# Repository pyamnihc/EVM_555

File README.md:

# EVM_555
The schematic and pcb are "a faithful and functional transistor-scale replica of the NE555 timer integrated circuit" from [a kit by Evil Mad Scientist](https://shop.evilmadscientist.com/productsmenu/922)

The schematic simulates the 555 timer as a astable multivibrator

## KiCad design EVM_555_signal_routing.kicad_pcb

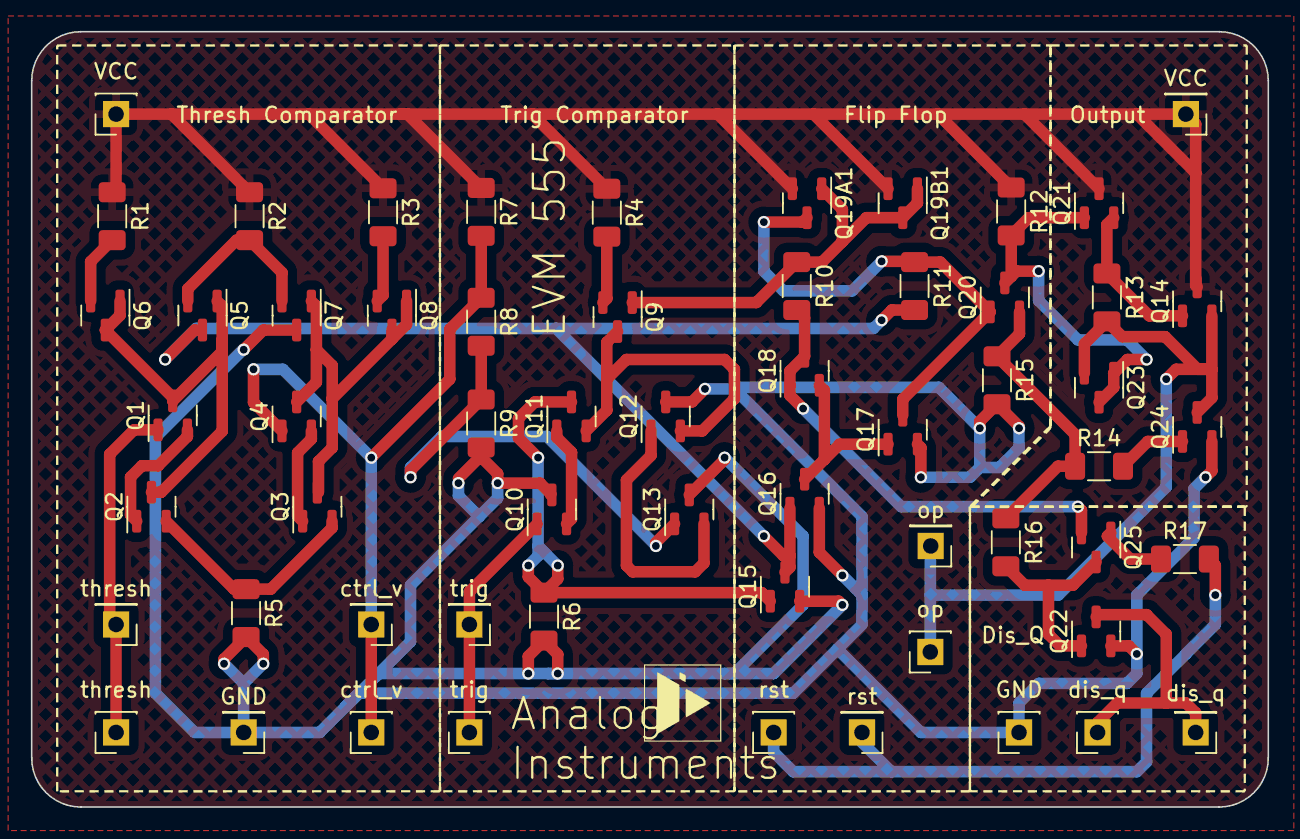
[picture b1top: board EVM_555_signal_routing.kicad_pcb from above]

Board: 2 copper layers, 80.0 x 50.2 mm, 59 parts (0 on the bottom side), 33 nets.

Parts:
J1: GND; PinHeader_1x01_P2.54mm_Vertical
J1A1: GND; PinSocket_1x01_P2.54mm_Vertical
J2: trig; PinHeader_1x01_P2.54mm_Vertical
J2A1: trig; PinSocket_1x01_P2.54mm_Vertical
J3: op; PinHeader_1x01_P2.54mm_Vertical
J3A1: op; PinSocket_1x01_P2.54mm_Vertical
J4: rst; PinHeader_1x01_P2.54mm_Vertical
J4A1: rst; PinSocket_1x01_P2.54mm_Vertical
J5: ctrl_v; PinHeader_1x01_P2.54mm_Vertical
J5A1: ctrl_v; PinSocket_1x01_P2.54mm_Vertical
J6: thresh; PinHeader_1x01_P2.54mm_Vertical
J6A1: thresh; PinSocket_1x01_P2.54mm_Vertical
J7: dis_q; PinHeader_1x01_P2.54mm_Vertical
J7A1: dis_q; PinSocket_1x01_P2.54mm_Vertical
J8: VCC; PinHeader_1x01_P2.54mm_Vertical
J8A1: VCC; PinSocket_1x01_P2.54mm_Vertical
Q1, Q2, Q3, Q4, Q14, Q15, Q16, Q17, Q18, Q20, Q21, Q22, Q24: MMBT3904; SOT-23
Q5, Q6, Q7, Q8, Q9, Q10, Q11, Q12, Q13, Q19A1, Q19B1, Q23, Q25: MMBT3906; SOT-23
R1, R3, R7, R8, R9, R11, R15: 4.7k; R_1206_3216Metric_Pad1.30x1.75mm_HandSolder
R2: 820; R_1206_3216Metric_Pad1.30x1.75mm_HandSolder
R4: 1k; R_1206_3216Metric_Pad1.30x1.75mm_HandSolder
R5: 10k; R_1206_3216Metric_Pad1.30x1.75mm_HandSolder
R6, R17: 100k; R_1206_3216Metric_Pad1.30x1.75mm_HandSolder
R10: 15k; R_1206_3216Metric_Pad1.30x1.75mm_HandSolder
R12: 6.8k; R_1206_3216Metric_Pad1.30x1.75mm_HandSolder
R13: 3.9k; R_1206_3216Metric_Pad1.30x1.75mm_HandSolder
R14: 220; R_1206_3216Metric_Pad1.30x1.75mm_HandSolder
R16: 100; R_1206_3216Metric_Pad1.30x1.75mm_HandSolder

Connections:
GND: J1.1, J1A1.1, Q7.3 (C), Q10.3 (C), Q12.3 (C), Q13.3 (C), Q15.2 (E), Q16.2 (E), Q17.2 (E), Q22.2 (E), Q24.2 (E), R5.2, R6.2, R9.2, R15.2
unnamed: Q1.3 (C), Q2.3 (C), Q5.1 (B), Q6.1 (B), Q6.3 (C)
unnamed: Q1.2 (E), Q2.1 (B)
unnamed: Q2.2 (E), Q3.2 (E), R5.1
unnamed: Q3.1 (B), Q4.2 (E)
unnamed: Q3.3 (C), Q4.3 (C), Q7.1 (B), Q8.1 (B), Q8.3 (C)
unnamed: Q5.2 (E), Q7.2 (E), R2.2
unnamed: Q6.2 (E), R1.2
unnamed: Q8.2 (E), R3.2
unnamed: Q9.2 (E), R4.2
unnamed: Q10.2 (E), Q11.1 (B)
unnamed: Q11.3 (C), Q15.1 (B), R6.1
unnamed: Q9.3 (C), Q11.2 (E), Q12.2 (E)
unnamed: Q12.1 (B), Q13.2 (E)
unnamed: Q13.1 (B), R8.2, R9.1
unnamed: Q14.1 (B), Q21.2 (E), R13.1
unnamed: Q16.3 (C), Q17.1 (B), Q18.2 (E)
unnamed: Q17.3 (C), Q19A1.3 (C), Q20.1 (B), R11.1
unnamed: Q18.1 (B), Q18.3 (C), Q25.2 (E), R10.2
unnamed: Q9.1 (B), Q19A1.1 (B), Q19B1.1 (B), Q19B1.3 (C), R10.1
unnamed: Q20.3 (C), Q21.1 (B), Q23.1 (B), Q23.3 (C), R12.2
unnamed: Q20.2 (E), R14.1, R15.1, R16.1
unnamed: Q22.1 (B), Q25.3 (C), R16.2
unnamed: Q24.1 (B), R14.2
unnamed: Q25.1 (B), R17.1
VCC: J8.1, J8A1.1, Q14.3 (C), Q19A1.2 (E), Q19B1.2 (E), Q21.3 (C), R1.1, R2.1, R3.1, R4.1, R7.1, R12.1
ctrl_v: J5.1, J5A1.1, Q4.1 (B), R7.2, R8.1
dis_q: J7.1, J7A1.1, Q22.3 (C)
op: J3.1, J3A1.1, Q14.2 (E), Q23.2 (E), Q24.3 (C), R13.2
rst: J4.1, J4A1.1, R17.2
thresh: J6.1, J6A1.1, Q1.1 (B)
thresh_out: Q5.3 (C), Q15.3 (C), Q16.1 (B), R11.2
trig: J2.1, J2A1.1, Q10.1 (B)

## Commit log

2023-05-19 fixed lib paths
2023-05-20 fixed fill zones
2023-05-20 add README.md
2023-05-21 fixed silkscreen
2023-05-21 pruned files
